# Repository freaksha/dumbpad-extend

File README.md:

an attempt to extend imchipwood's dumbpad

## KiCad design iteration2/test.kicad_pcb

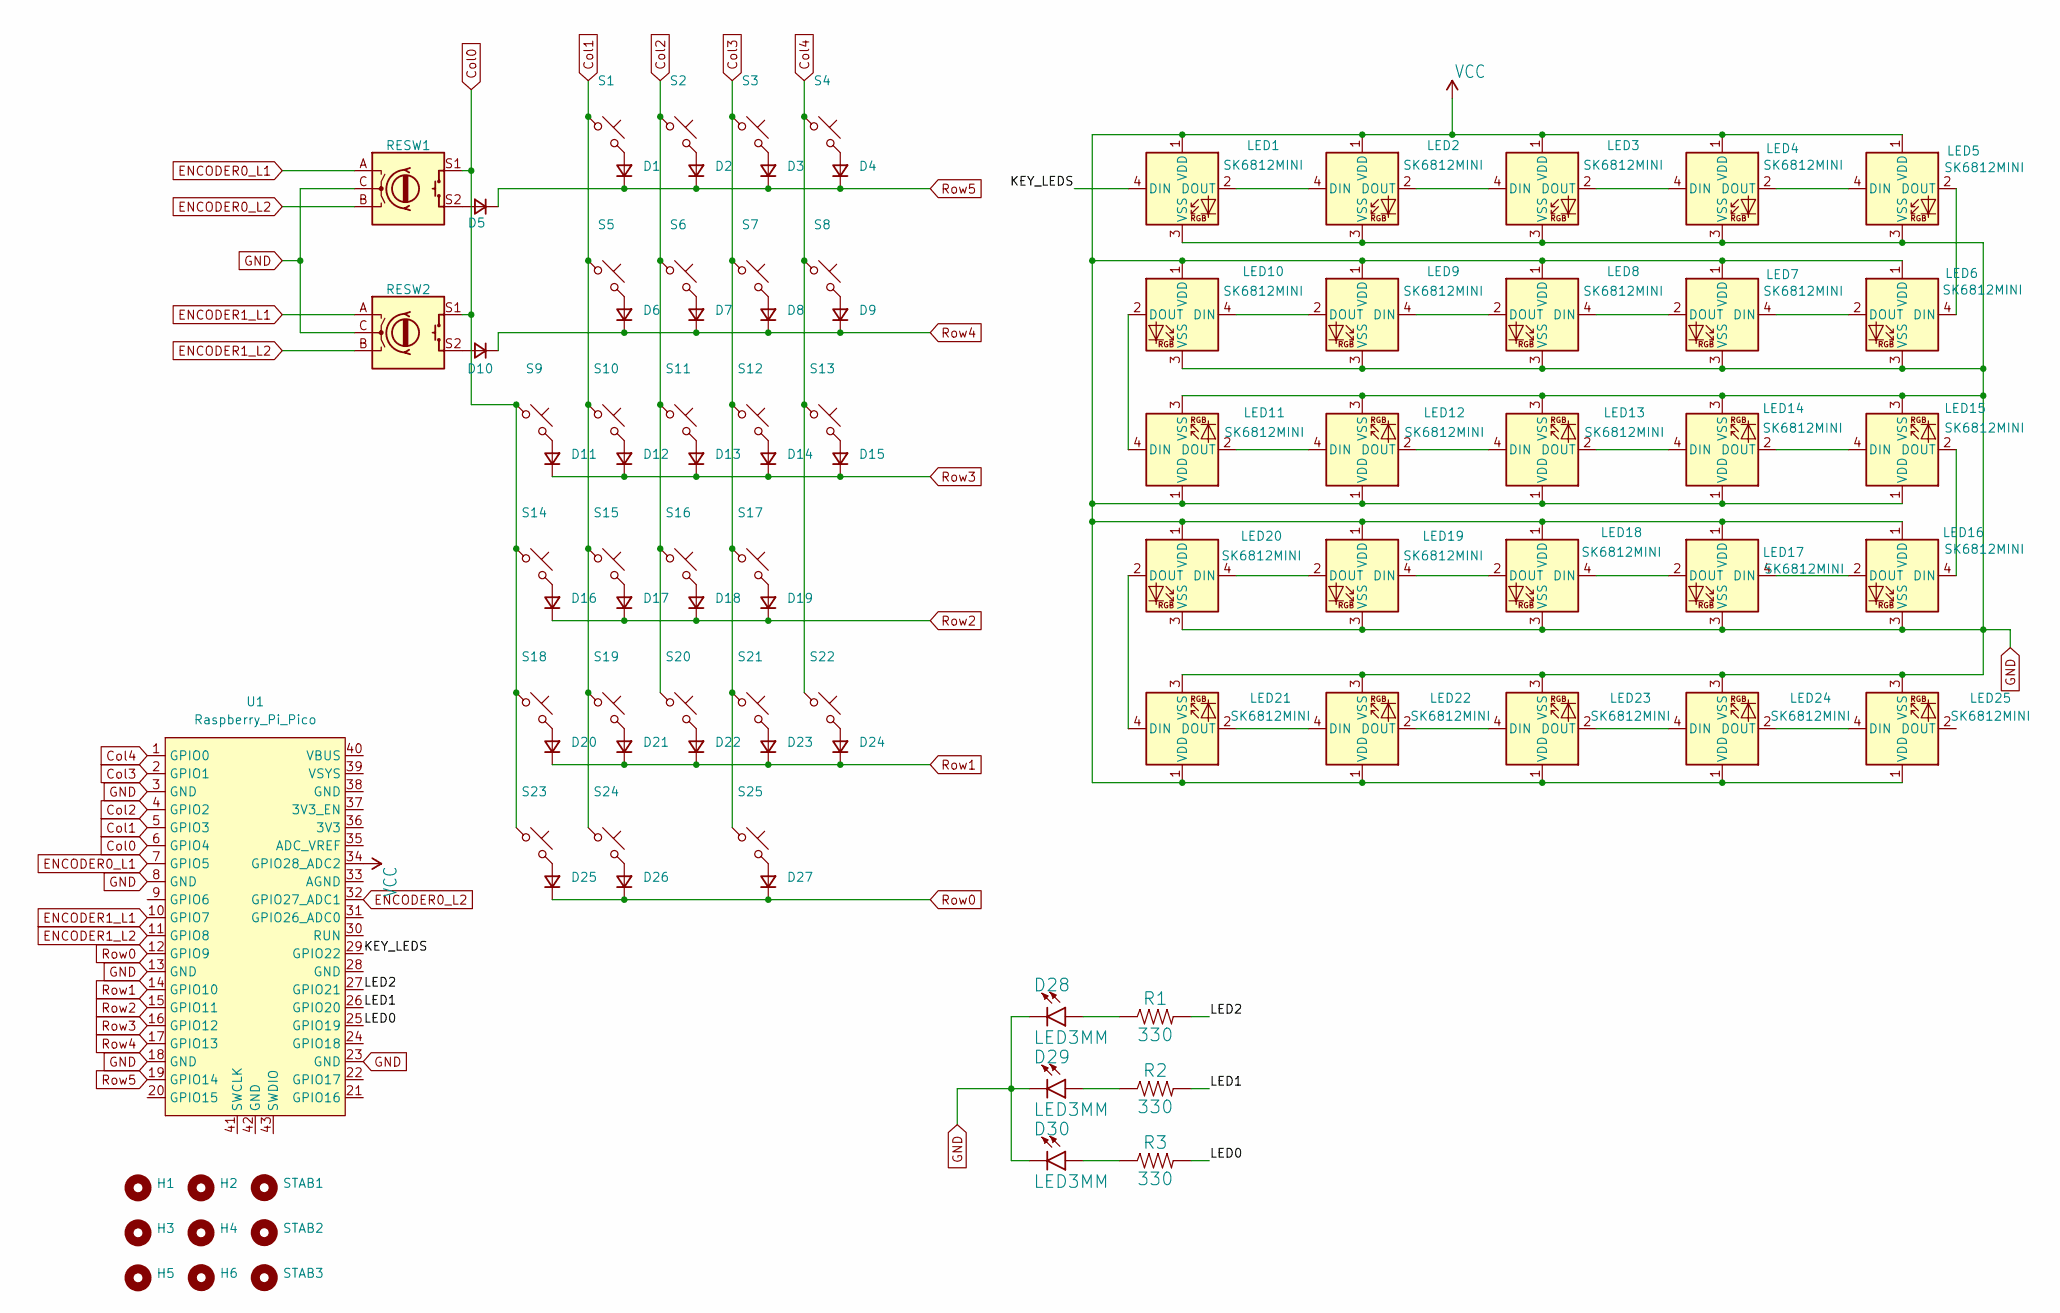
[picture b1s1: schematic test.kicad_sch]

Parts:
D1, D2, D3, D4, D5, D6, D7, D8, D9, D10, D11, D12, D13, D14, D15, D16, D17, D18, D19, D20, D21, D22, D23, D24, D25, D26, D27: D_SOD-123
D28, D29, D30: LED3MM; LED_3MM
H1, H2, H3, H4, H5, H6: MountingHole_2.2mm_M2_DIN965
LED1, LED2, LED3, LED4, LED5, LED6, LED7, LED8, LED9, LED10, LED11, LED12, LED13, LED14, LED15, LED16, LED17, LED18, LED19, LED20, LED21, LED22, LED23, LED24, LED25: SK6812MINI; LED_SK6812MINI_PLCC4_3.5x3.5mm_P1.75mm
R1, R2, R3: 330; AXIAL-0.3
RESW1, RESW2: RotaryEncoder_Alps_EC11E-Switch_Vertical_H20mm_CircularMoun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
S1, S2, S3, S4, S5, S6, S7, S8, S9, S10, S11, S12, S14, S15, S16, S17, S18, S19, S20, S21, S23, S25: Hotswap_MX_1.00u
S13, S22: Hotswap_MX_2.00u_90deg
S24: Hotswap_MX_2.00u
STAB1, STAB2, STAB3: Stabilizer_MX_2.00u
U1: Raspberry_Pi_Pico

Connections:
/KEY_LEDS: LED1.4 (DIN), U1.29 (GPIO22)
/LED0: R3.P$2 (2), U1.25 (GPIO19)
/LED1: R2.P$2 (2), U1.26 (GPIO20)
/LED2: R1.P$2 (2), U1.27 (GPIO21)
Col0: RESW1.S1, RESW2.S1, S9.1, S14.1, S18.1, S23.1, U1.6 (GPIO4)
Col1: S1.1, S5.1, S10.1, S15.1, S19.1, S24.1, U1.5 (GPIO3)
Col2: S2.1, S6.1, S11.1, S16.1, S20.1, U1.4 (GPIO2)
Col3: S3.1, S7.1, S12.1, S17.1, S21.1, S25.1, U1.2 (GPIO1)
Col4: S4.1, S8.1, S13.1, S22.1, U1.1 (GPIO0)
ENCODER0_L1: RESW1.A, U1.7 (GPIO5)
ENCODER0_L2: RESW1.B, U1.32 (GPIO27_ADC1)
ENCODER1_L1: RESW2.A, U1.10 (GPIO7)
ENCODER1_L2: RESW2.B, U1.11 (GPIO8)
GND: D28.K (C), D29.K (C), D30.K (C), LED1.3 (VSS), LED2.3 (VSS), LED3.3 (VSS), LED4.3 (VSS), LED5.3 (VSS), LED6.3 (VSS), LED7.3 (VSS), LED8.3 (VSS), LED9.3 (VSS), LED10.3 (VSS), LED11.3 (VSS), LED12.3 (VSS), LED13.3 (VSS), LED14.3 (VSS), LED15.3 (VSS), LED16.3 (VSS), LED17.3 (VSS), LED18.3 (VSS), LED19.3 (VSS), LED20.3 (VSS), LED21.3 (VSS), LED22.3 (VSS), LED23.3 (VSS), LED24.3 (VSS), LED25.3 (VSS), RESW1.C, RESW2.C, U1.3 (GND), U1.8 (GND), U1.13 (GND), U1.18 (GND), U1.23 (GND)
unnamed: D1.2 (A), S1.2
unnamed: D2.2 (A), S2.2
unnamed: D3.2 (A), S3.2
unnamed: D4.2 (A), S4.2
unnamed: D5.2 (A), RESW1.S2
unnamed: D6.2 (A), S5.2
unnamed: D7.2 (A), S6.2
unnamed: D8.2 (A), S7.2
unnamed: D9.2 (A), S8.2
unnamed: D10.2 (A), RESW2.S2
unnamed: D11.2 (A), S9.2
unnamed: D12.2 (A), S10.2
unnamed: D13.2 (A), S11.2
unnamed: D14.2 (A), S12.2
unnamed: D15.2 (A), S13.2
unnamed: D16.2 (A), S14.2
unnamed: D17.2 (A), S15.2
unnamed: D18.2 (A), S16.2
unnamed: D19.2 (A), S17.2
unnamed: D20.2 (A), S18.2
unnamed: D21.2 (A), S19.2
unnamed: D22.2 (A), S20.2
unnamed: D23.2 (A), S21.2
unnamed: D24.2 (A), S22.2
unnamed: D25.2 (A), S23.2
unnamed: D26.2 (A), S24.2
unnamed: D27.2 (A), S25.2
unnamed: LED1.2 (DOUT), LED2.4 (DIN)
unnamed: LED2.2 (DOUT), LED3.4 (DIN)
unnamed: LED3.2 (DOUT), LED4.4 (DIN)
unnamed: LED4.2 (DOUT), LED5.4 (DIN)
unnamed: LED5.2 (DOUT), LED6.4 (DIN)
unnamed: LED6.2 (DOUT), LED7.4 (DIN)
unnamed: LED7.2 (DOUT), LED8.4 (DIN)
unnamed: LED8.2 (DOUT), LED9.4 (DIN)
unnamed: LED9.2 (DOUT), LED10.4 (DIN)
unnamed: LED10.2 (DOUT), LED11.4 (DIN)
unnamed: LED11.2 (DOUT), LED12.4 (DIN)
unnamed: LED12.2 (DOUT), LED13.4 (DIN)
unnamed: LED13.2 (DOUT), LED14.4 (DIN)
unnamed: LED14.2 (DOUT), LED15.4 (DIN)
unnamed: LED15.2 (DOUT), LED16.4 (DIN)
unnamed: LED16.2 (DOUT), LED17.4 (DIN)
unnamed: LED17.2 (DOUT), LED18.4 (DIN)
unnamed: LED18.2 (DOUT), LED19.4 (DIN)
unnamed: LED19.2 (DOUT), LED20.4 (DIN)
unnamed: LED20.2 (DOUT), LED21.4 (DIN)
unnamed: LED21.2 (DOUT), LED22.4 (DIN)
unnamed: LED22.2 (DOUT), LED23.4 (DIN)
unnamed: LED23.2 (DOUT), LED24.4 (DIN)
unnamed: LED24.2 (DOUT), LED25.4 (DIN)
unnamed: D28.A, R1.P$1 (1)
unnamed: D29.A, R2.P$1 (1)
unnamed: D30.A, R3.P$1 (1)
Row0: D25.1 (K), D26.1 (K), D27.1 (K), U1.12 (GPIO9)
Row1: D20.1 (K), D21.1 (K), D22.1 (K), D23.1 (K), D24.1 (K), U1.14 (GPIO10)
Row2: D16.1 (K), D17.1 (K), D18.1 (K), D19.1 (K), U1.15 (GPIO11)
Row3: D11.1 (K), D12.1 (K), D13.1 (K), D14.1 (K), D15.1 (K), U1.16 (GPIO12)
Row4: D6.1 (K), D7.1 (K), D8.1 (K), D9.1 (K), D10.1 (K), U1.17 (GPIO13)
Row5: D1.1 (K), D2.1 (K), D3.1 (K), D4.1 (K), D5.1 (K), U1.19 (GPIO14)
VCC: LED1.1 (VDD), LED2.1 (VDD), LED3.1 (VDD), LED4.1 (VDD), LED5.1 (VDD), LED6.1 (VDD), LED7.1 (VDD), LED8.1 (VDD), LED9.1 (VDD), LED10.1 (VDD), LED11.1 (VDD), LED12.1 (VDD), LED13.1 (VDD), LED14.1 (VDD), LED15.1 (VDD), LED16.1 (VDD), LED17.1 (VDD), LED18.1 (VDD), LED19.1 (VDD), LED20.1 (VDD), LED21.1 (VDD), LED22.1 (VDD), LED23.1 (VDD), LED24.1 (VDD), LED25.1 (VDD), U1.34 (GPIO28_ADC2)

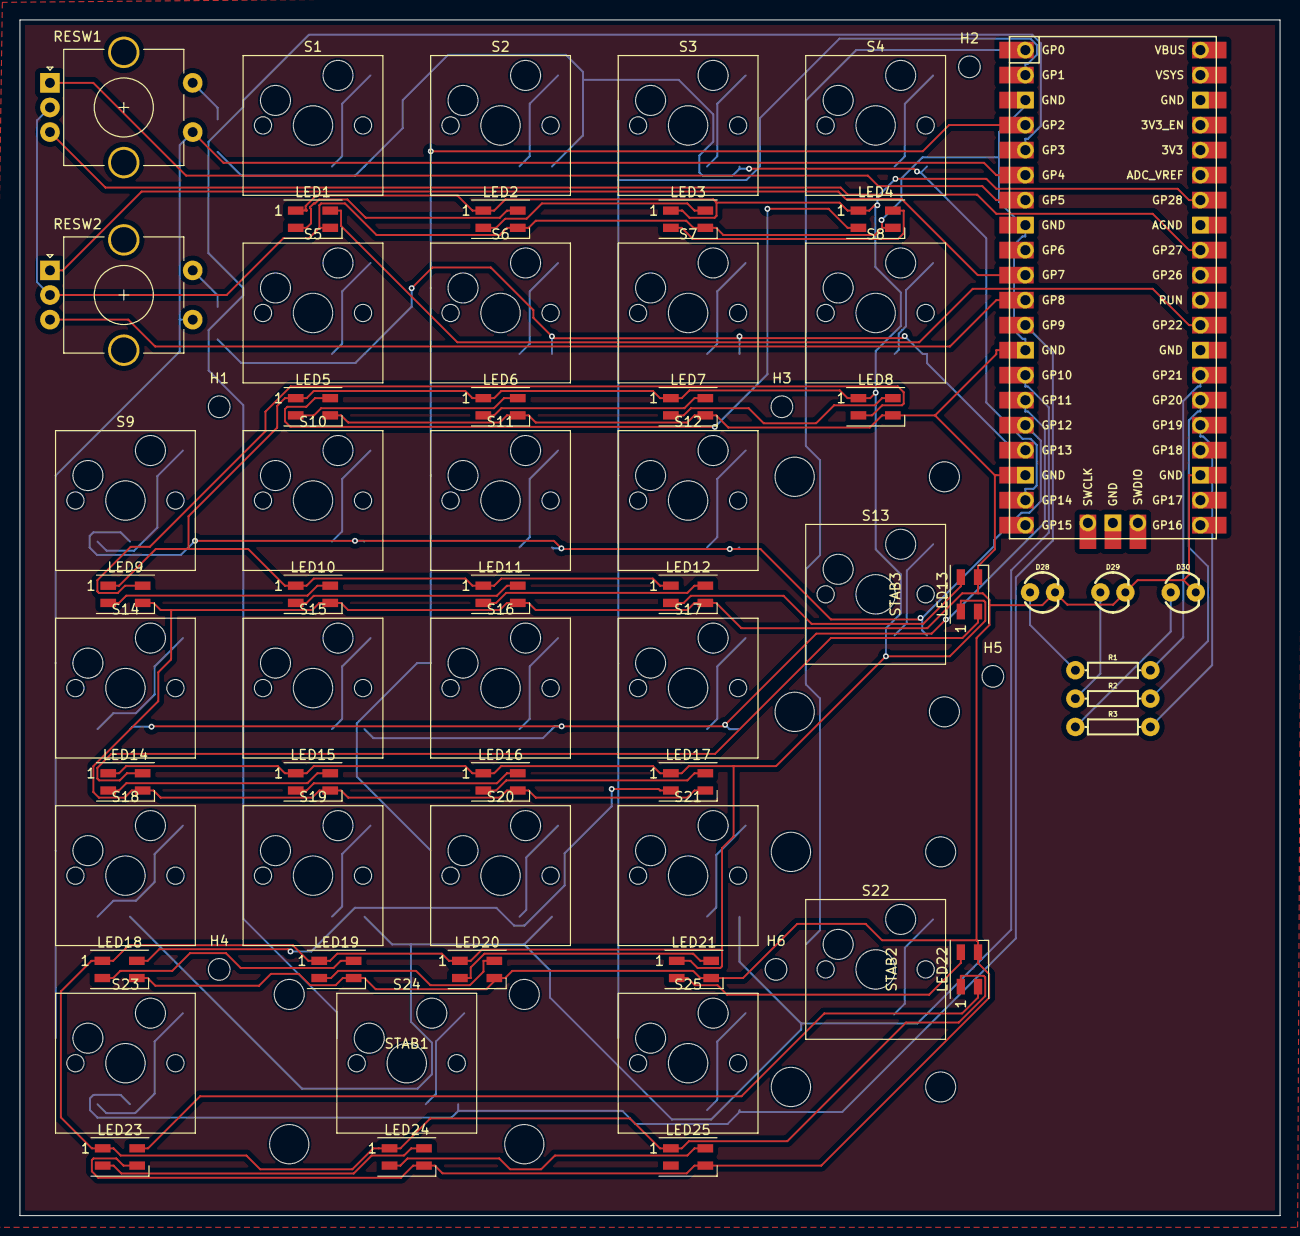
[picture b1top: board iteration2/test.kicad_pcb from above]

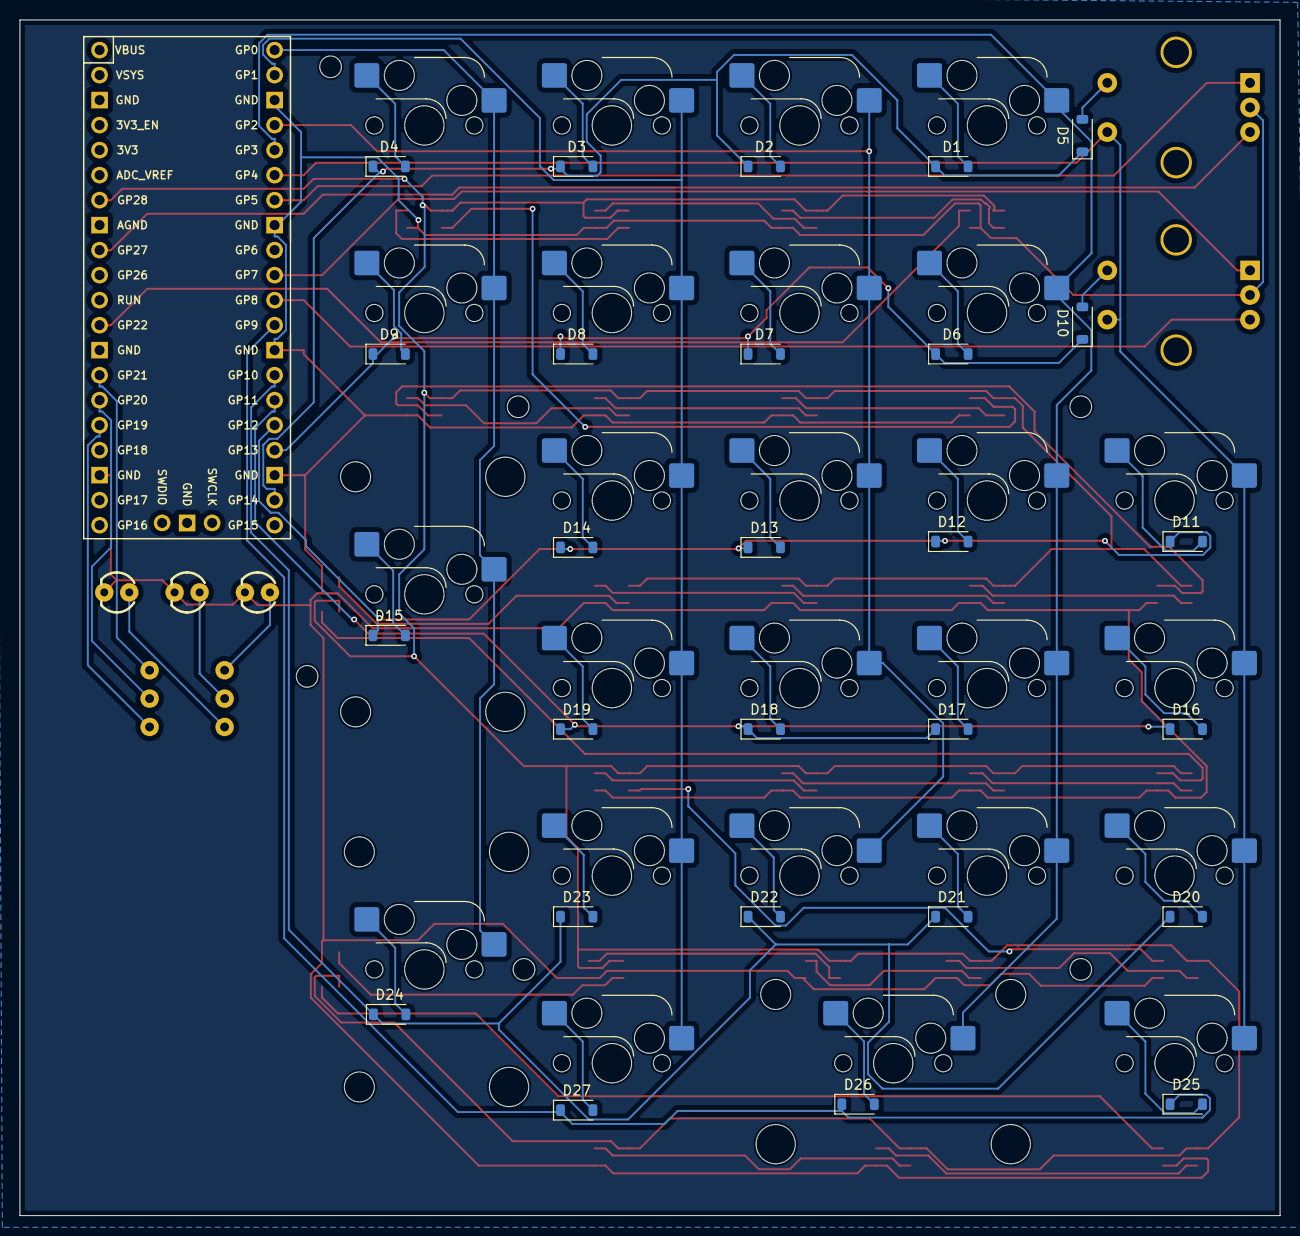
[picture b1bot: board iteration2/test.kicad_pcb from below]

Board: 2 copper layers, 128.0 x 121.4 mm, 95 parts (27 on the bottom side), 75 nets.

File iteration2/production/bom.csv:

Designator,Footprint,Quantity,Value,LCSC Part #
"D1, D10, D11, D12, D13, D14, D15, D16, D17, D18, D19, D2, D20, D21, D22, D23, D24, D25, D26, D27, D3, D4, D5, D6, D7, D8, D9",D_SOD-123,27,~,
"D28, D29, D30",LED_3MM,3,LED3MM,
"H1, H2, H3, H4, H5, H6",MountingHole_2.2mm_M2_DIN965,6,~,
"LED1, LED10, LED11, LED12, LED13, LED14, LED15, LED16, LED17, LED18, LED19, LED2, LED20, LED21, LED22, LED23, LED24, LED25, LED3, LED4, LED5, LED6, LED7, LED8, LED9",LED_SK6812MINI_PLCC4_3.5x3.5mm_P1.75mm,25,SK6812MINI,
"R1, R2, R3",AXIAL-0.3,3,330,
"RESW1, RESW2",RotaryEncoder_Alps_EC11E-Switch_Vertical_H20mm_CircularMountingHoles,2,~,
"S1, S10, S11, S12, S14, S15, S16, S17, S18, S19, S2, S20, S21, S23, S25, S3, S4, S5, S6, S7, S8, S9",Hotswap_MX_1.00u,22,~,
"S13, S22",Hotswap_MX_2.00u_90deg,2,~,
S24,Hotswap_MX_2.00u,1,~,
"STAB1, STAB2, STAB3",Stabilizer_MX_2.00u,3,~,
U1,Raspberry_Pi_Pico,1,Raspberry_Pi_Pico,

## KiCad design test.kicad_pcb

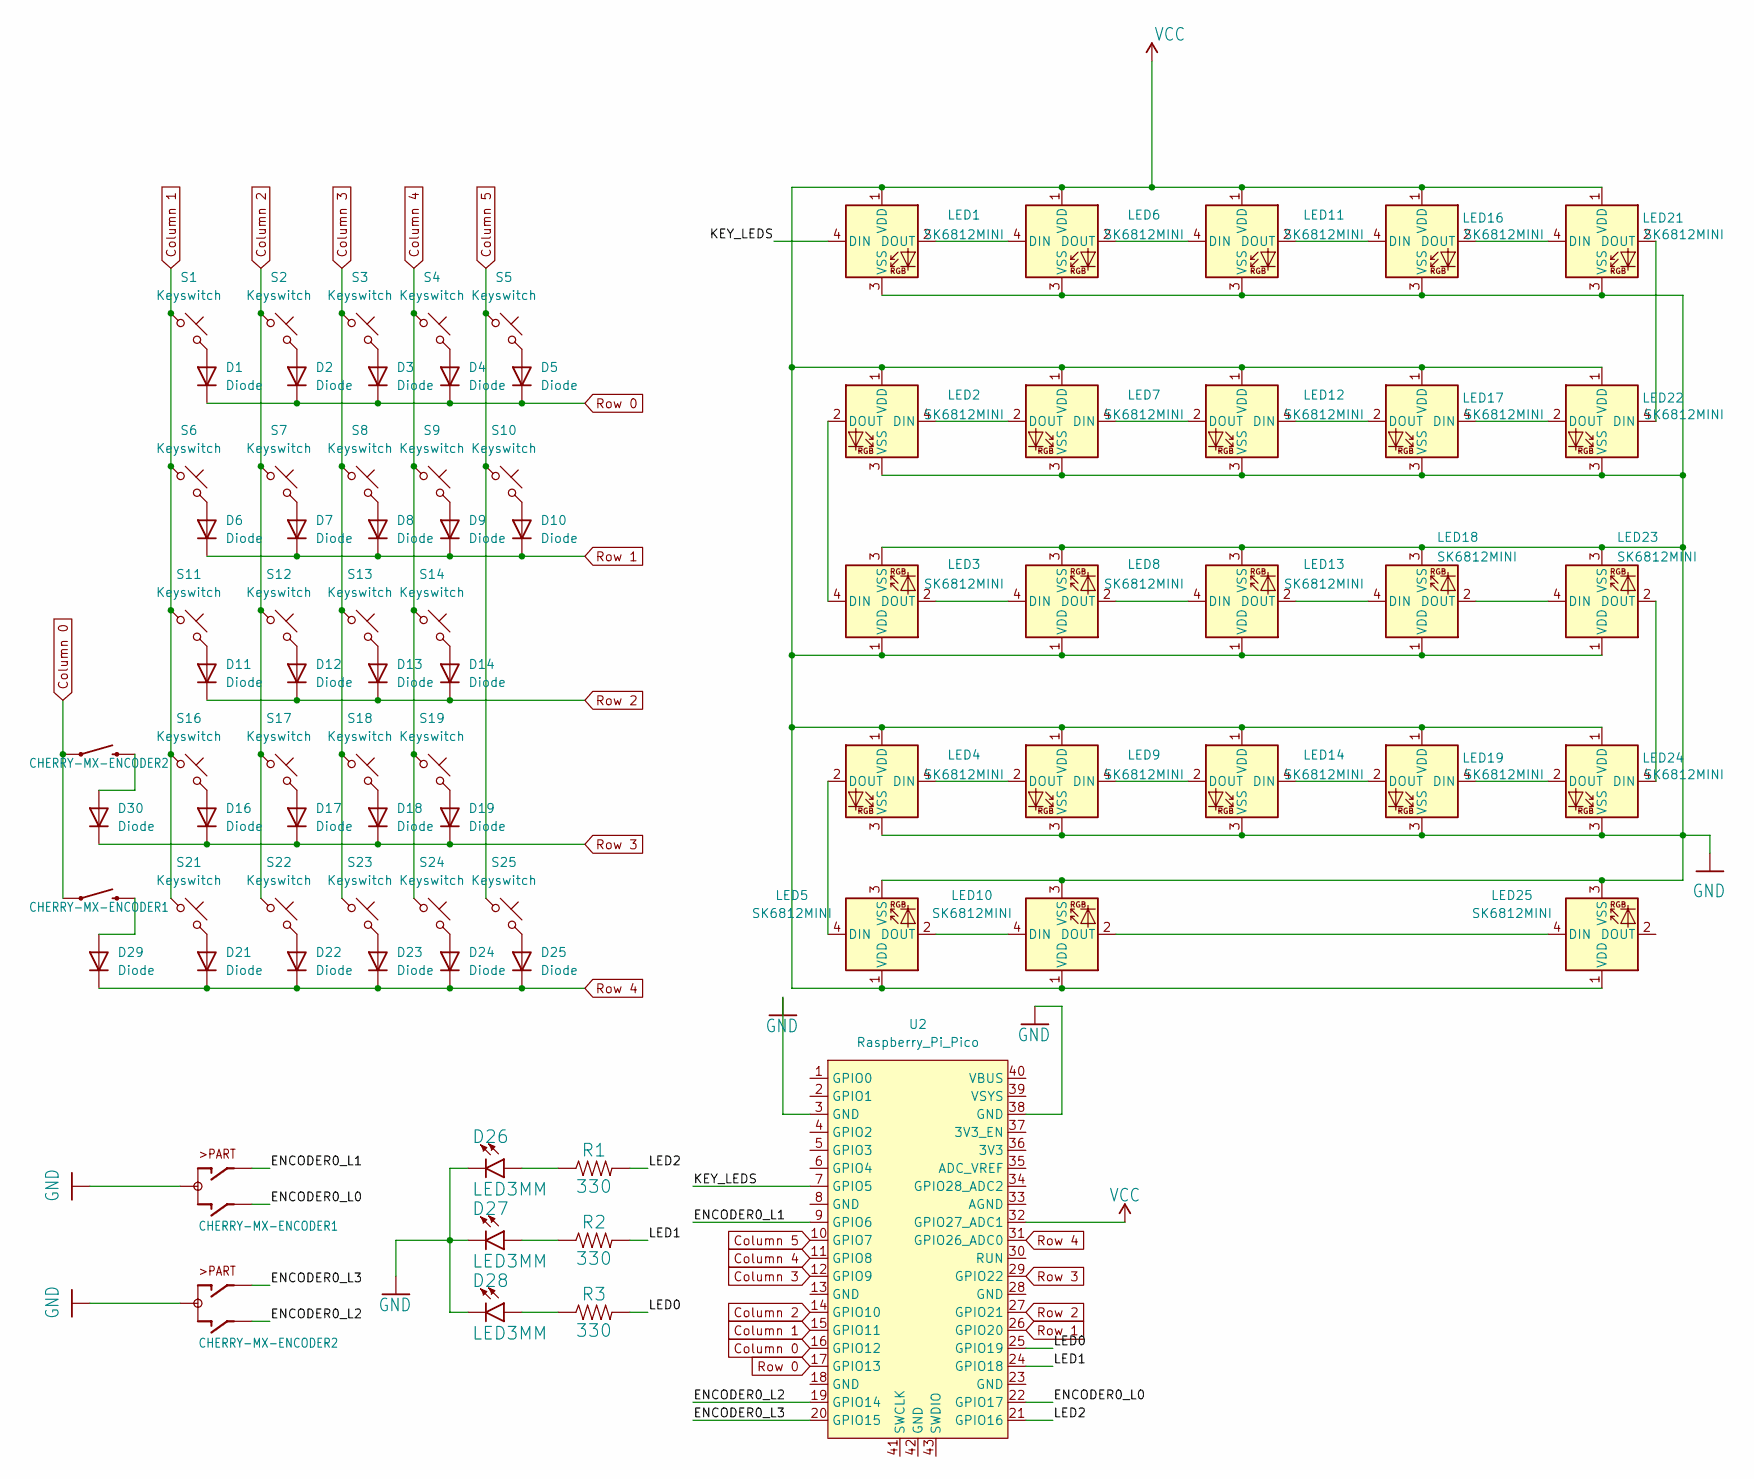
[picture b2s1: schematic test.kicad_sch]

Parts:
D1, D2, D3, D4, D5, D6, D7, D8, D9, D10, D11, D12, D13, D14, D16, D17, D18, D19, D21, D22, D23, D24, D25, D29, D30: Diode; Diode_DO-35
D26, D27, D28: LED3MM; LED_3MM
LED1, LED2, LED3, LED4, LED5, LED6, LED7, LED8, LED9, LED10, LED11, LED12, LED13, LED14, LED16, LED17, LED18, LED19, LED21, LED22, LED23, LED24, LED25: SK6812MINI; LED_SK6812MINI_PLCC4_3.5x3.5mm_P1.75mm
R1, R2, R3: 330; AXIAL-0.3
RE_3_1: CHERRY-MX-ENCODER1; RotaryEncoder_Alps_EC11E-Switch_Vertical_H20mm
RE_3_2: CHERRY-MX-ENCODER2; RotaryEncoder_Alps_EC11E-Switch_Vertical_H20mm
S1, S2, S3, S4, S5, S6, S7, S8, S9, S11, S12, S13, S14, S16, S17, S18, S19, S21, S22, S23, S24: Keyswitch; Hotswap_MX_1.00u
S10, S25: Keyswitch; Hotswap_MX_2.00u_90deg
U2: Raspberry_Pi_Pico

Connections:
/ENCODER0_L0: RE_3_1.B, U2.22 (GPIO17)
/ENCODER0_L1: RE_3_1.A, U2.9 (GPIO6)
/ENCODER0_L2: RE_3_2.B, U2.19 (GPIO14)
/ENCODER0_L3: RE_3_2.A, U2.20 (GPIO15)
/KEY_LEDS: LED1.4 (DIN), U2.7 (GPIO5)
/LED0: R3.P$2 (2), U2.25 (GPIO19)
/LED1: R2.P$2 (2), U2.24 (GPIO18)
/LED2: R1.P$2 (2), U2.21 (GPIO16)
Column 0: RE_3_1.D (1), RE_3_1.S1 (1), RE_3_2.D (1), RE_3_2.S1 (1), U2.16 (GPIO12)
Column 1: S1.1, S6.1, S11.1, S16.1, S21.1, U2.15 (GPIO11)
Column 2: S2.1, S7.1, S12.1, S17.1, S22.1, U2.14 (GPIO10)
Column 3: S3.1, S8.1, S13.1, S18.1, S23.1, U2.12 (GPIO9)
Column 4: S4.1, S9.1, S14.1, S19.1, S24.1, U2.11 (GPIO8)
Column 5: S5.1, S10.1, S25.1, U2.10 (GPIO7)
GND: D26.K (C), D27.K (C), D28.K (C), LED1.3 (VSS), LED2.3 (VSS), LED3.3 (VSS), LED4.3 (VSS), LED5.3 (VSS), LED6.3 (VSS), LED7.3 (VSS), LED8.3 (VSS), LED9.3 (VSS), LED10.3 (VSS), LED11.3 (VSS), LED12.3 (VSS), LED13.3 (VSS), LED14.3 (VSS), LED16.3 (VSS), LED17.3 (VSS), LED18.3 (VSS), LED19.3 (VSS), LED21.3 (VSS), LED22.3 (VSS), LED23.3 (VSS), LED24.3 (VSS), LED25.3 (VSS), RE_3_1.C, RE_3_2.C, U2.3 (GND), U2.38 (GND)
unnamed: D1.2 (A), S1.2
unnamed: D2.2 (A), S2.2
unnamed: D3.2 (A), S3.2
unnamed: D4.2 (A), S4.2
unnamed: D5.2 (A), S5.2
unnamed: D6.2 (A), S6.2
unnamed: D7.2 (A), S7.2
unnamed: D8.2 (A), S8.2
unnamed: D9.2 (A), S9.2
unnamed: D10.2 (A), S10.2
unnamed: D11.2 (A), S11.2
unnamed: D12.2 (A), S12.2
unnamed: D13.2 (A), S13.2
unnamed: D14.2 (A), S14.2
unnamed: D16.2 (A), S16.2
unnamed: D17.2 (A), S17.2
unnamed: D18.2 (A), S18.2
unnamed: D19.2 (A), S19.2
unnamed: D21.2 (A), S21.2
unnamed: D22.2 (A), S22.2
unnamed: D23.2 (A), S23.2
unnamed: D24.2 (A), S24.2
unnamed: D25.2 (A), S25.2
unnamed: D29.2 (A), RE_3_1.E (2), RE_3_1.S2 (2)
unnamed: D30.2 (A), RE_3_2.E (2), RE_3_2.S2 (2)
unnamed: LED1.2 (DOUT), LED6.4 (DIN)
unnamed: LED2.4 (DIN), LED7.2 (DOUT)
unnamed: LED2.2 (DOUT), LED3.4 (DIN)
unnamed: LED3.2 (DOUT), LED8.4 (DIN)
unnamed: LED4.4 (DIN), LED9.2 (DOUT)
unnamed: LED4.2 (DOUT), LED5.4 (DIN)
unnamed: LED5.2 (DOUT), LED10.4 (DIN)
unnamed: LED10.2 (DOUT), LED25.4 (DIN)
unnamed: LED6.2 (DOUT), LED11.4 (DIN)
unnamed: LED11.2 (DOUT), LED16.4 (DIN)
unnamed: LED12.4 (DIN), LED17.2 (DOUT)
unnamed: LED7.4 (DIN), LED12.2 (DOUT)
unnamed: LED8.2 (DOUT), LED13.4 (DIN)
unnamed: LED13.2 (DOUT), LED18.4 (DIN)
unnamed: LED14.4 (DIN), LED19.2 (DOUT)
unnamed: LED9.4 (DIN), LED14.2 (DOUT)
unnamed: LED16.2 (DOUT), LED21.4 (DIN)
unnamed: LED17.4 (DIN), LED22.2 (DOUT)
unnamed: LED18.2 (DOUT), LED23.4 (DIN)
unnamed: LED19.4 (DIN), LED24.2 (DOUT)
unnamed: LED21.2 (DOUT), LED22.4 (DIN)
unnamed: LED23.2 (DOUT), LED24.4 (DIN)
unnamed: D26.A, R1.P$1 (1)
unnamed: D27.A, R2.P$1 (1)
unnamed: D28.A, R3.P$1 (1)
Row 0: D1.1 (K), D2.1 (K), D3.1 (K), D4.1 (K), D5.1 (K), U2.17 (GPIO13)
Row 1: D6.1 (K), D7.1 (K), D8.1 (K), D9.1 (K), D10.1 (K), U2.26 (GPIO20)
Row 2: D11.1 (K), D12.1 (K), D13.1 (K), D14.1 (K), U2.27 (GPIO21)
Row 3: D16.1 (K), D17.1 (K), D18.1 (K), D19.1 (K), D30.1 (K), U2.29 (GPIO22)
Row 4: D21.1 (K), D22.1 (K), D23.1 (K), D24.1 (K), D25.1 (K), D29.1 (K), U2.31 (GPIO26_ADC0)
VCC: LED1.1 (VDD), LED2.1 (VDD), LED3.1 (VDD), LED4.1 (VDD), LED5.1 (VDD), LED6.1 (VDD), LED7.1 (VDD), LED8.1 (VDD), LED9.1 (VDD), LED10.1 (VDD), LED11.1 (VDD), LED12.1 (VDD), LED13.1 (VDD), LED14.1 (VDD), LED16.1 (VDD), LED17.1 (VDD), LED18.1 (VDD), LED19.1 (VDD), LED21.1 (VDD), LED22.1 (VDD), LED23.1 (VDD), LED24.1 (VDD), LED25.1 (VDD), U2.32 (GPIO27_ADC1)

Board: 2 copper layers, 80 parts (25 on the bottom side), 71 nets, no tracks yet.

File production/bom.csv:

Designator,Footprint,Quantity,Value,LCSC Part #
"D1, D10, D11, D12, D13, D14, D15, D16, D17, D18, D19, D2, D20, D21, D22, D23, D24, D25, D29, D3, D30, D4, D5, D6, D7, D8, D9",Diode_DO-35,27,Diode,
"D26, D27, D28",LED_3MM,3,LED3MM,
"LED1, LED10, LED11, LED12, LED13, LED14, LED15, LED16, LED17, LED18, LED19, LED2, LED20, LED21, LED22, LED23, LED24, LED25, LED3, LED4, LED5, LED6, LED7, LED8, LED9",LED_SK6812MINI_PLCC4_3.5x3.5mm_P1.75mm,25,SK6812MINI,
"R1, R2, R3",AXIAL-0.3,3,330,
RE_3_1,RotaryEncoder_Alps_EC11E-Switch_Vertical_H20mm,1,CHERRY-MX-ENCODER1,
RE_3_2,RotaryEncoder_Alps_EC11E-Switch_Vertical_H20mm,1,CHERRY-MX-ENCODER2,
"S1, S10, S11, S12, S13, S14, S15, S16, S17, S18, S19, S2, S20, S21, S22, S23, S24, S25, S3, S4, S5, S6, S7, S8, S9",Hotswap_MX_1.00u,25,Keyswitch,
U2,Raspberry_Pi_Pico,1,Raspberry_Pi_Pico,

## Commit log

2024-03-24 Arrange PCB to 5x5 button layout and 2 rotary encoder
2024-03-24 deleting unneeded files
2024-03-25 Update layout to mimic normal NumPad
2024-03-26 rearrange folder
2024-03-26 Add second iteration
2024-04-25 update layout
